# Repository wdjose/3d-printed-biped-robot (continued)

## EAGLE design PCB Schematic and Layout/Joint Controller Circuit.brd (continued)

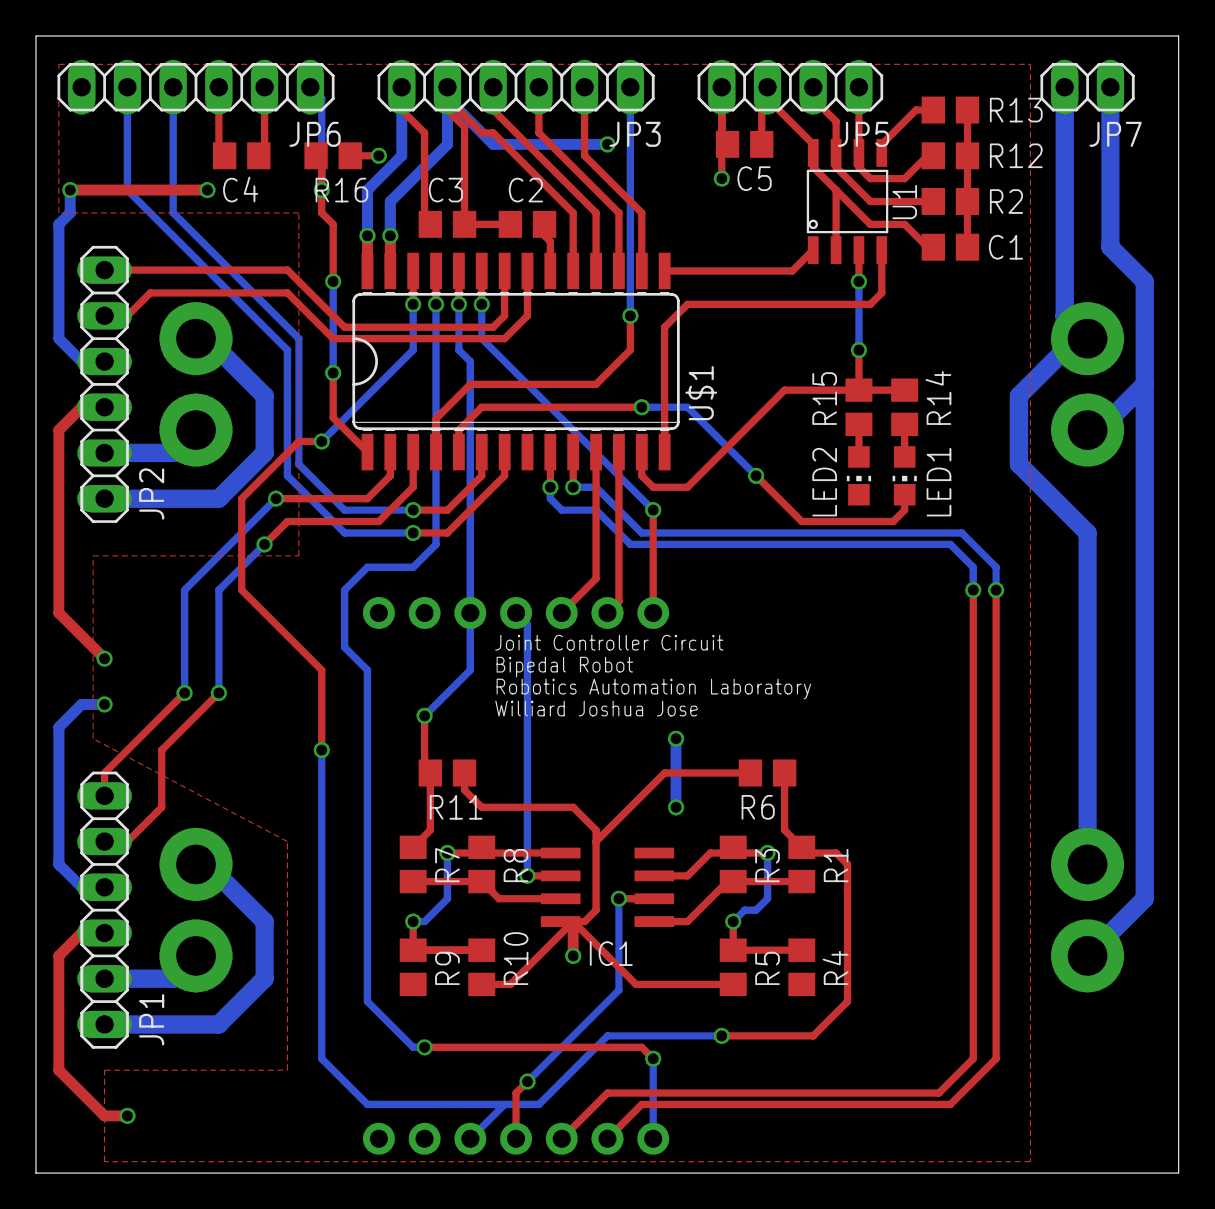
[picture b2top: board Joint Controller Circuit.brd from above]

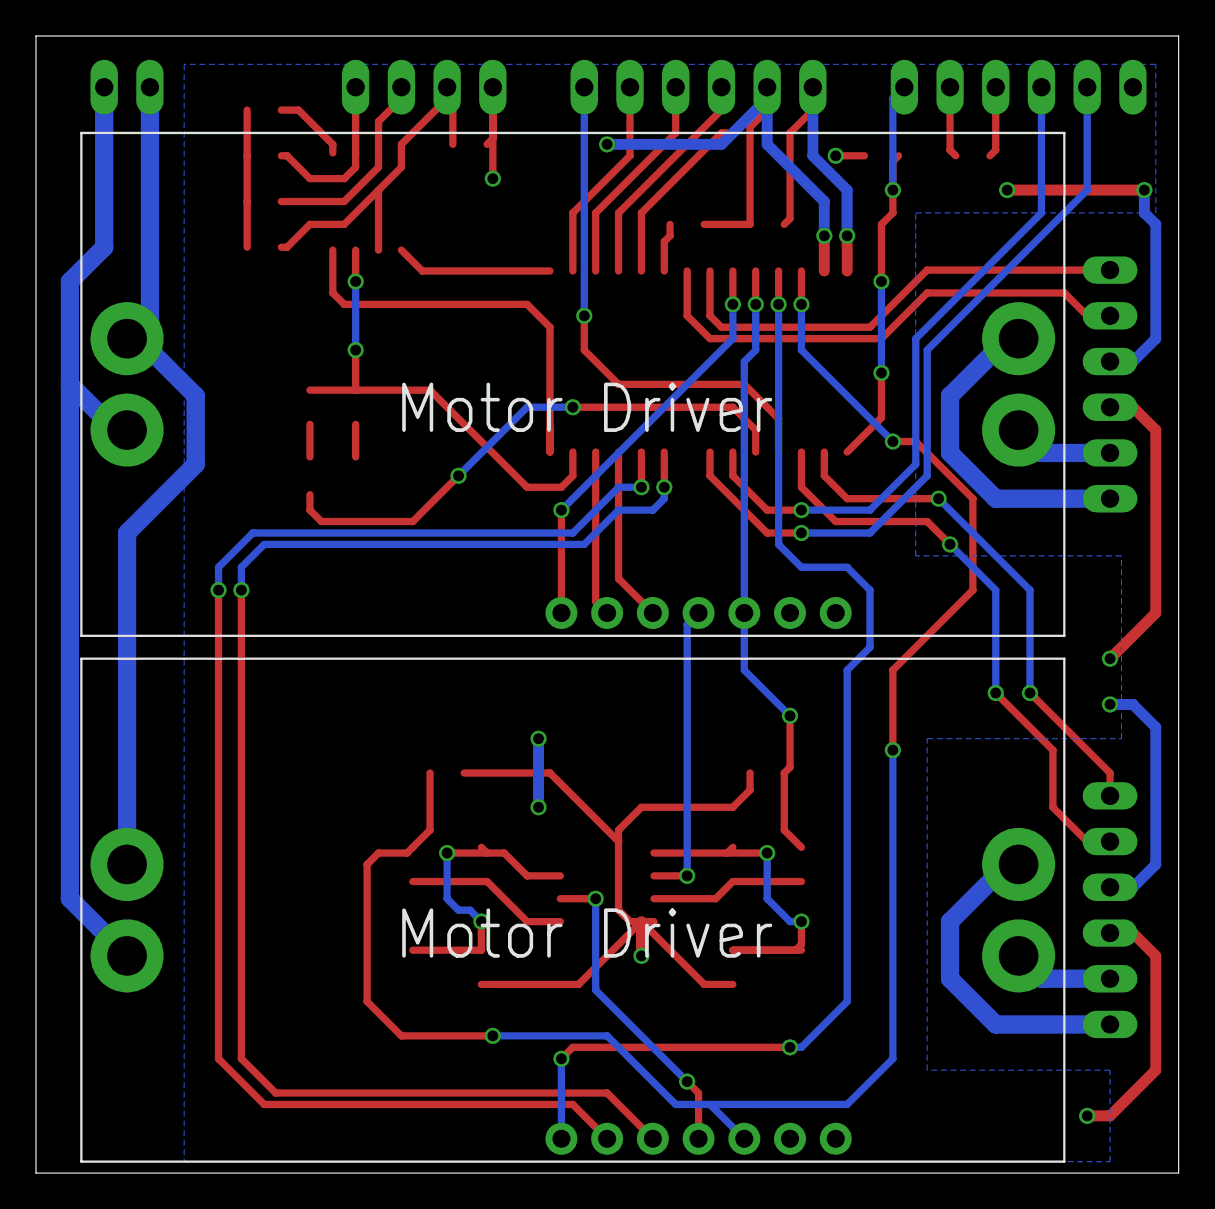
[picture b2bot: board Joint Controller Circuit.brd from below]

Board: 2 copper layers, 63.5 x 63.2 mm, 34 parts (2 on the bottom side), 43 nets.

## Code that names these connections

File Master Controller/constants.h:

#ifndef CONSTANTS_H
#define	CONSTANTS_H

//controller ID
#define CONTROLLER_ID 0
#define SELF (0xf0 + CONTROLLER_ID)

//frequencies
#define FRC 7372800                 //FRC = 7.3728 MHz +-1%
#define FOSC (FRC/4*150/2)          //FOSC = 138.24 MHz
#define FCY (FOSC/2)                //FCY = 69.12 MHz
#define FBAUD(x) ((FCY/x)/4-1)      //FBAUD(115200) = 149

//led outputs
#define LED1 _LATB12
#define LED2 _LATB13
#define LED3 _LATA10
#define LED4 _LATA7
#define LED5 _LATB14
#define LED6 _LATB15
#define LED7 _LATG6
#define LED8 _LATG7
#define LED9 _LATG8
#define LED10 _LATG9
#define LED11 _LATA12
#define LED12 _LATA11
#define LED13 _LATA0
#define LED14 _LATA1
#define LED15 _LATB0
#define LED16 _LATB1

//pushbuttons
#define PB1 _RC4
#define PB2 _RC5
#define PB3 _RC12
#define PB4 _RC15
#define PB5 _RD8

#endif

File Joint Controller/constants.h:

#ifndef CONSTANTS_H
#define	CONSTANTS_H

//controller ID
#define CONTROLLER_ID 6
#define SELF (0xf0 + CONTROLLER_ID)

//frequencies
#define FRC 7372800                 //FRC = 7.3728 MHz +-1%
#define FOSC (FRC/4*150/2)          //FOSC = 138.24 MHz
#define FCY (FOSC/2)                //FCY = 69.12 MHz
#define FBAUD(x) ((FCY/x)/4-1)      //FBAUD(115200) = 149

//digital inputs
#define ENCA1 _RA1
#define ENCB1 _RA0
#define ENCA2 _RB10
#define ENCB2 _RB11

//digital outputs
#define INA1 _LATA2
#define INB1 _LATA3
#define INA2 _LATB4
#define INB2 _LATA4
#define EN1 _LATB15
#define EN2 _LATB13
#define LED _LATB1

//PWM duty cycles
#define PWM1 PDC1
#define PWM2 PDC2

#endif

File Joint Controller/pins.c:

#include "init.h"

void Init_Pins()
{
	//disable all analog pins
    ANSELA = 0;
    ANSELB = 0;
	
	//set all pins to LOW by default
	LATA = 0;
	LATB = 0;
	
    //set encoders as digital input
	_TRISA1 = 1;			//ENCA1
	_TRISA0 = 1;			//ENCB1
	_TRISB10 = 1;			//ENCA2
	_TRISB11 = 1;			//ENCB2
	
	//set H-bridge outputs as digital output
	_TRISA2 = 0;			//INA1
	_TRISA3 = 0;			//INB1
	_TRISB4 = 0;			//INA2
	_TRISA4 = 0;			//INB2
	
	//set enable outputs as digital output open drain
	_TRISB15 = 0;			//EN1
	_ODCB15 = 1;			//open drain
	_LATB15 = 0;
	_TRISB13 = 0;			//EN2
	_ODCB13 = 1;			//open drain
	_LATB13 = 0;
	
	//set PWM outputs as digital output and PWM
	_TRISB14 = 0;			//PWM1
	_LATB14 = 1;
	_TRISB12 = 0;			//PWM2
	_LATB12 = 1;
	
	//set LED as digital output
	_TRISB1 = 0;			//LED
	_LATB1 = 1;				//LED off default
	
	//set UART pins as digital input/output
	_TRISB9 = 1;			//RX
	_TRISB8 = 1;			//TX
	
	//set CAN pins as digital input
	_TRISB5 = 1;			//CANRX
	_TRISB6 = 1;			//CANTX
}

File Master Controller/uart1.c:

#include "init.h"

#define BUFSIZE 128
#define BUFMASK (BUFSIZE - 1)

volatile int UART1_size;
volatile int UART1_start, UART1_end;
uint8_t UART1_buffer[BUFSIZE];

void Init_UART1() {
	UART1_start = 0;
	UART1_end = 0;
	UART1_size = 0;
	
	//map UART1 TXD pin to pin RP49 (RC1)
	RPOR5bits.RP49R = 0b000001;
	//map UART1 TXD pin to pin RP20 (RA4 SDO1)
	RPOR0bits.RP20R = 0b000001;
	//map UART1 RXD pin to pin RP41 (RC0)
	RPINR18bits.U1RXR = 48;
	
	U1MODEbits.STSEL = 0;			//1 stop bit
	U1MODEbits.PDSEL = 0;			//no parity, 8 data bits
	U1MODEbits.ABAUD = 0;			//auto baud disabled
	U1MODEbits.BRGH = 1;			//high speed mode (4 clocks per bit)
	U1BRG = FBAUD(115200);			//baud rate set to 115200
	U1STAbits.URXISEL = 0;			//interrupt after one rx done
	
	_U1RXIF = 0;					//clear uart receive interrupt flag
	_U1RXIP = 4;					//set uart receive interrupt priority to 4
	_U1RXIE = 1;					//enable uart rx interrupt
	
	U1MODEbits.UARTEN = 1;			//enable uart
	U1STAbits.UTXEN = 1;			//enable uart transmissions
	delay_ms(1);					//delay 1ms to ensure tx is ready
}

void UART1_puts(char *s) {
	while (*s)
		UART1_write(*s++);
	UART1_write('\n');
}

void UART1_print(char *s) {
	while (*s)
		UART1_write(*s++);
}

void UART1_write(char c) {
	while (U1STAbits.UTXBF);
	U1TXREG = c;
}

uint8_t UART1_read() {
	if (UART1_size) {
		uint8_t ret = UART1_buffer[UART1_start];
		
		UART1_start = (UART1_start + 1) & BUFMASK;
		UART1_size--;
		
		return ret;
	}
	return 0;
}

void UART1_process() {
	
}

void __attribute__((interrupt, no_auto_psv)) _U1RXInterrupt() {
	uint8_t data = U1RXREG;
	int UART1_next = (UART1_end + 1) & 0b1111111;
	if (UART1_next != UART1_start) {
		UART1_buffer[UART1_end] = data;
		UART1_end = UART1_next;
		UART1_size++;
	}
	
    _U1RXIF = 0;
}

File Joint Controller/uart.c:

#include "init.h"

#define BUFSIZE 128
#define BUFMASK (BUFSIZE - 1)

volatile int UART_size;

volatile int UART_start, UART_end;
uint8_t UART_buffer[BUFSIZE];

void Init_UART() {
	//clear UART receive ring buffer
	UART_start = 0;
	UART_end = 0;
	UART_size = 0;
	
	//map UART1 TXD pin to pin RP40 (RB8 SDO1)
	//RPOR3bits.RP40R = 0b000001;	//disabled to prevent TX pins from interfering with each other
	//map UART1 RXD pin to pin RP41 (RB9 SDI1)
	RPINR18bits.U1RXR = 41;
	
	U1MODEbits.STSEL = 0;			//1 stop bit
	U1MODEbits.PDSEL = 0;			//no parity, 8 data bits
	U1MODEbits.ABAUD = 0;			//auto baud disabled
	U1MODEbits.BRGH = 1;			//high speed mode (4 clocks per bit)
	U1BRG = FBAUD(115200);			//baud rate set to 115200
	U1STAbits.URXISEL = 0;			//interrupt after one rx done
	
	_U1RXIF = 0;					//clear uart receive interrupt flag
	_U1RXIP = 4;					//set uart receive interrupt priority to 4
	_U1RXIE = 1;					//enable uart rx interrupt
	
	U1MODEbits.UARTEN = 1;			//enable uart
	U1STAbits.UTXEN = 1;			//enable uart transmissions
	delay_ms(1);					//delay 1ms to ensure tx is ready
}

void UART_puts(char *s) {
	while (*s)
		UART_write(*s++);
	UART_write('\n');
}

void UART_print(char *s) {
	while (*s)
		UART_write(*s++);
}

void UART_write(char c) {
	while (U1STAbits.UTXBF);
	U1TXREG = c;
}

uint8_t UART_read() {
	if (UART_size) {
		uint8_t ret = UART_buffer[UART_start];
		
		UART_start = (UART_start + 1) & BUFMASK;
		UART_size--;
		
		return ret;
	}
	return 0;
}

void UART_process() {
	if (flags.packetrx)
		return;
	if (UART_size >= 11) {
		if (UART_buffer[UART_start] == 0x55) {
			if (UART_buffer[(UART_start + 10) & BUFMASK] == 0xAA) {
				int checksum = 0;
				int UART_ctr = (UART_start + 8) & BUFMASK;
				while (UART_ctr != UART_start) {
					unsigned int v = UART_buffer[UART_ctr];
					while (v) {
						checksum += v & 1;
						v >>= 1;
					}
					UART_ctr = (UART_ctr - 1) & BUFMASK;
				}
				if (UART_buffer[(UART_start + 9) & BUFMASK] == checksum) {
					packet.ID = UART_buffer[(UART_start + 1) & BUFMASK] & 0xFF;
					packet.Command = UART_buffer[(UART_start + 2) & BUFMASK] & 0xFF;
					packet.Options1 = UART_buffer[(UART_start + 3) & BUFMASK] & 0xFF;
					packet.Options2 = UART_buffer[(UART_start + 4) & BUFMASK] & 0xFF;
					packet.Value1 = (UART_buffer[(UART_start + 5) & BUFMASK] & 0xFF) << 8;
					packet.Value1 |= UART_buffer[(UART_start + 6) & BUFMASK] & 0xFF;
					packet.Value2 = (UART_buffer[(UART_start + 7) & BUFMASK] & 0xFF) << 8;
					packet.Value2 |= UART_buffer[(UART_start + 8) & BUFMASK] & 0xFF;
					
					UART_start = (UART_start + 11) & BUFMASK;
					UART_size -= 11;
					
					if (packet.ID == CONTROLLER_ID)
						flags.packetrx = 1;
					return;
				}
			}
		}
		UART_start = (UART_start + 1) & BUFMASK;
		UART_size--;
	}
}

void __attribute__((interrupt, no_auto_psv)) _U1RXInterrupt() {
	uint8_t data = U1RXREG;
	int UART_next = (UART_end + 1) & 0b1111111;
	if (UART_next != UART_start) {
		UART_buffer[UART_end] = data;
		UART_end = UART_next;
		UART_size++;
	}
	
    _U1RXIF = 0;
}

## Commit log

2018-08-21 Added SolidWorks 3D model of biped
2018-08-21 Added Joint Controller MPLAB project files
2018-08-21 Added Master Controller MPLAB project files
2018-08-21 Added EAGLE files for the schematic and layout of the joint and master controllers
2018-08-21 Updated README.md with project description
